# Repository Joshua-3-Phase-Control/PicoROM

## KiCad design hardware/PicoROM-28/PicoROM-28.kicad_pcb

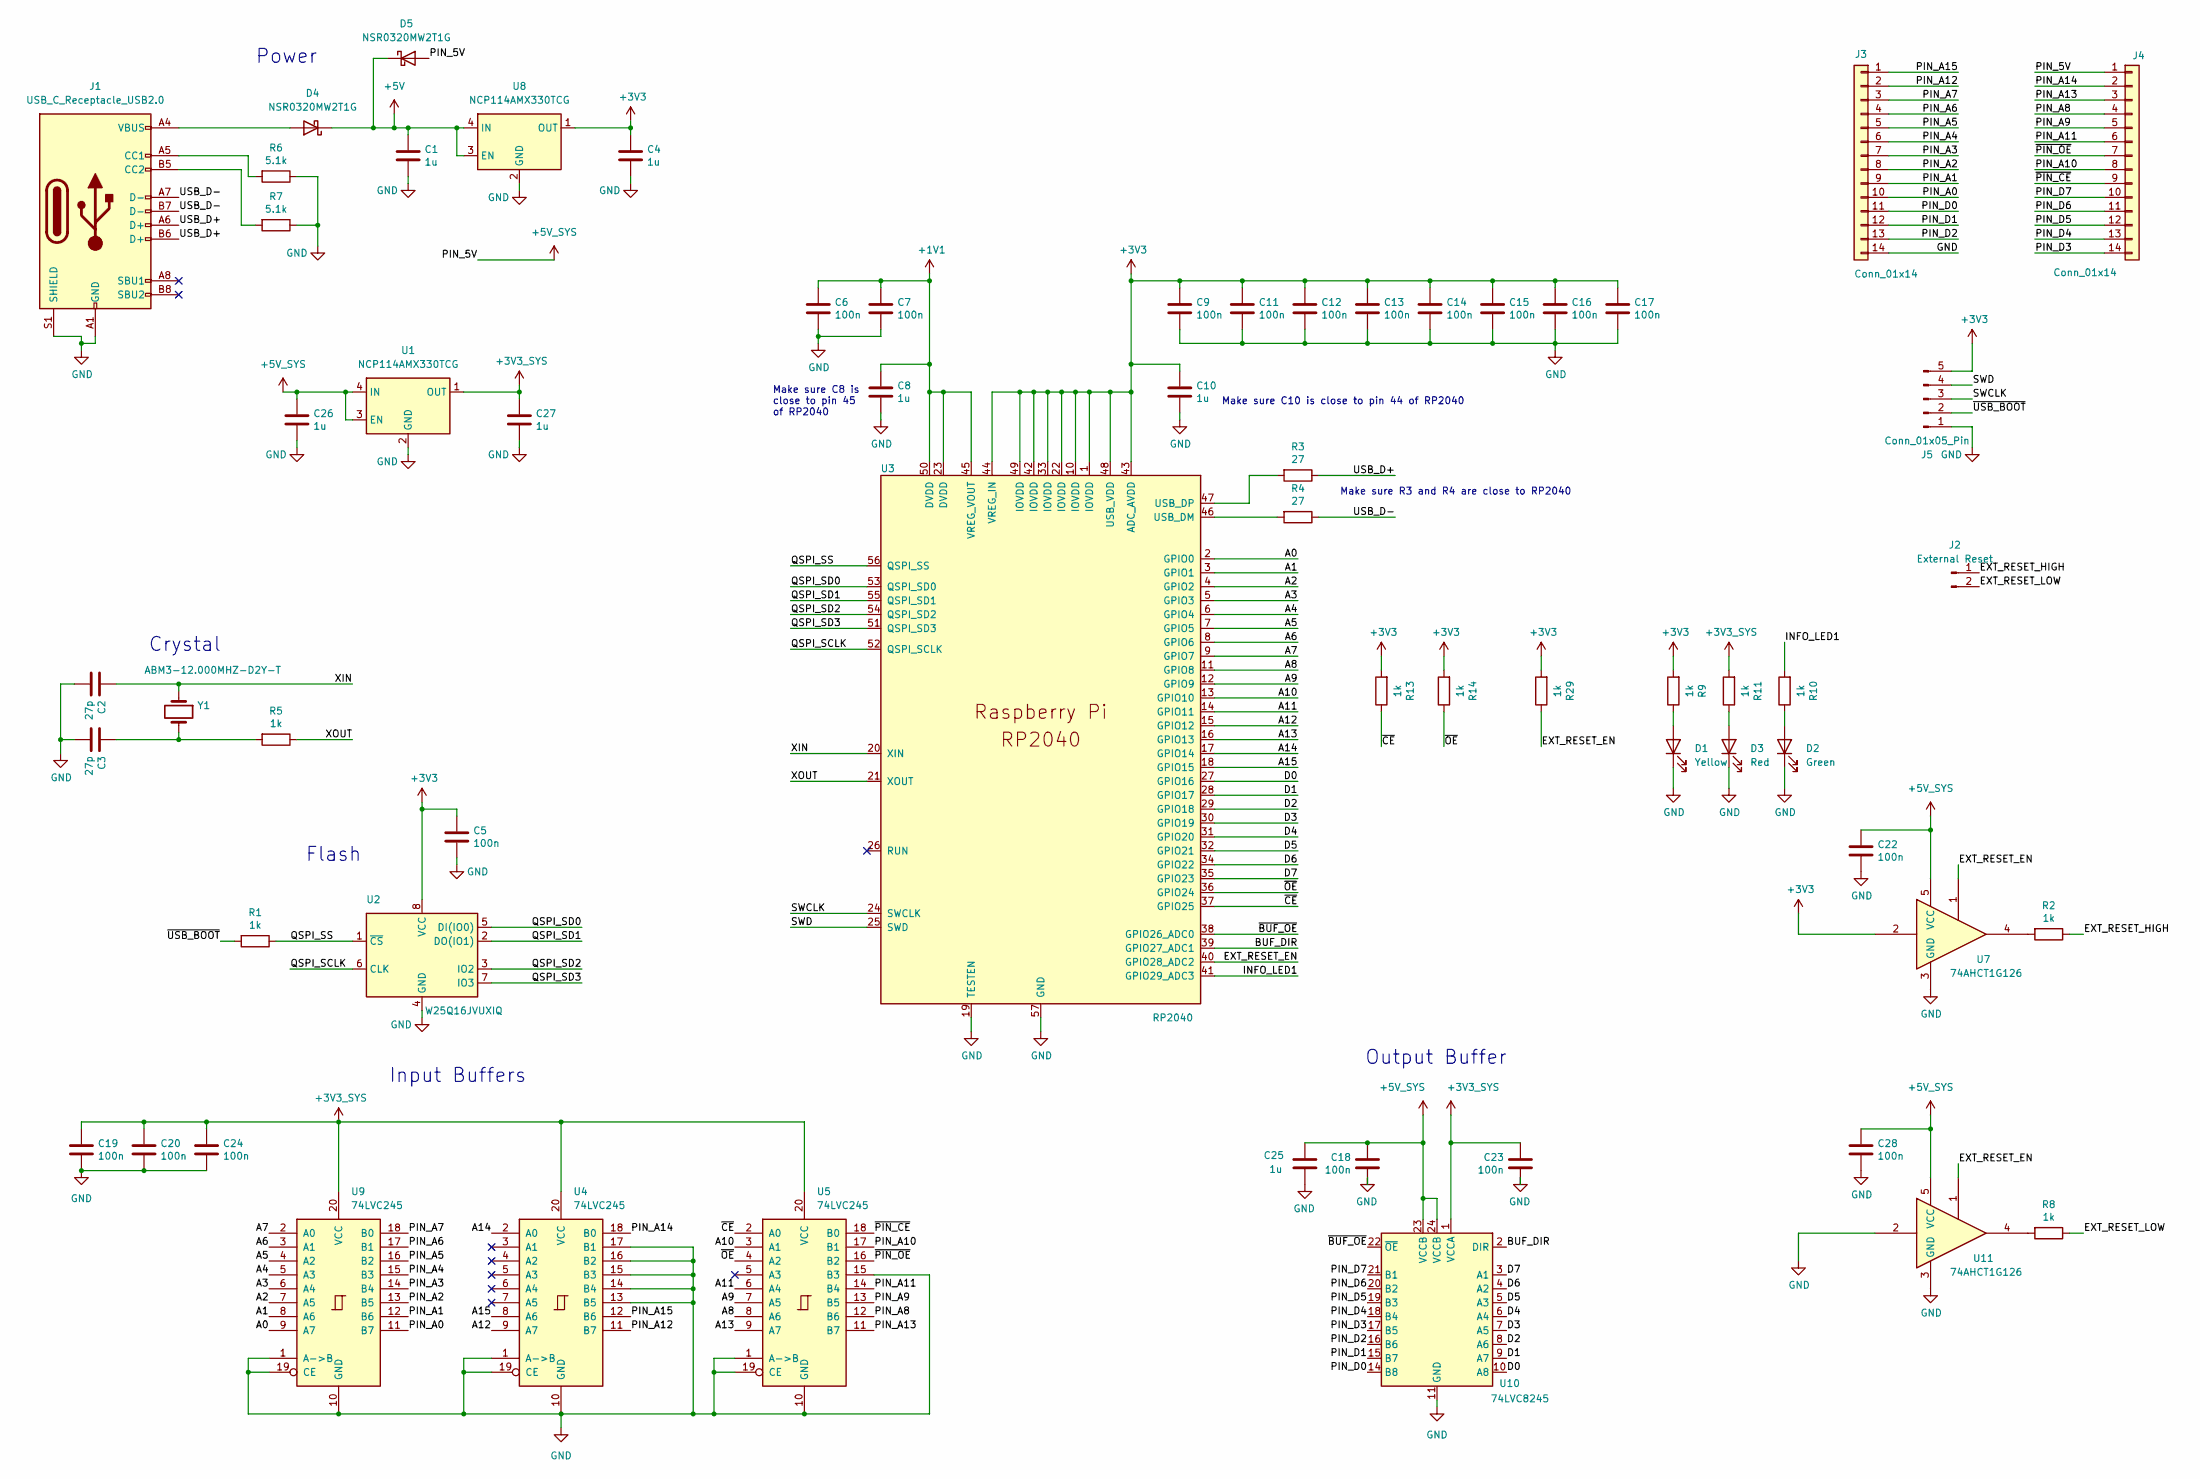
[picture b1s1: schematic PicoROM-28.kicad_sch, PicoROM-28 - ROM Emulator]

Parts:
C1, C4, C8, C10, C25, C26, C27: 1u; C_0402_1005Metric; MPN C52923
C2, C3: 27p; C_0402_1005Metric; MPN C1557
C5, C6, C7, C9, C11, C12, C13, C14, C15, C16, C17, C18, C19, C20, C22, C23, C24, C28: 100n; C_0201_0603Metric; MPN C307380
D1: Yellow; LED_0402_1005Metric; MPN C434450
D2: Green; LED_0402_1005Metric; MPN C74338
D3: Red; LED_0402_1005Metric; MPN C510305
D4, D5: NSR0320MW2T1G; D_SOD-323; MPN C48192
J1: USB_C_Receptacle_USB2.0; USB_C_Receptacle_HRO_TYPE-C-31-M-12; MPN C165948
J2: External Reset; PinHeader_1x02_P2.54mm_Vertical
J3, J4: Conn_01x14; PinHeader_1x14_P2.54mm_Vertical
J5: Conn_01x05_Pin; PinHeader_1x05_P1.27mm_Vertical
R1, R2, R5, R8, R9, R10, R11, R13, R14, R29: 1k; R_0201_0603Metric; MPN C270335
R3, R4: 27; R_0201_0603Metric; MPN C473051
R6, R7: 5.1k; R_0201_0603Metric; MPN C473460
U1, U8: NCP114AMX330TCG; OnSemi_XDFN4-1EP_1.0x1.0mm_EP0.52x0.52mm; MPN C133056
U2: W25Q16JVUXIQ; Winbond_USON-8-1EP_3x2mm_P0.5mm_EP0.2x1.6mm; MPN C7466821
U3: RP2040; RP2040-QFN-56; MPN C2040
U4, U5, U9: 74LVC245; V-QFN4525-20_L4.5-W2.5-P0.50-BL; MPN C294612
U7, U11: 74AHCT1G126; SOT-353_SC-70-5; MPN C52140433
U10: 74LVC8245; DHVQFN24_L5.5-W3.5-P0.50-BL-EP; MPN C548858
Y1: ABM3-12.000MHZ-D2Y-T; Crystal_SMD_5032-2Pin_5.0x3.2mm; MPN C148313

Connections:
+1V1: C6.1, C7.1, C8.1, U3.23 (DVDD), U3.45 (VREG_VOUT), U3.50 (DVDD)
+3V3: C4.1, C5.1, C9.1, C10.1, C11.1, C12.1, C13.1, C14.1, C15.1, C16.1, C17.1, J5.5, R9.2, R13.2, R14.2, R29.2, U2.8 (VCC), U3.1 (IOVDD), U3.10 (IOVDD), U3.22 (IOVDD), U3.33 (IOVDD), U3.42 (IOVDD), U3.43 (ADC_AVDD), U3.44 (VREG_IN), U3.48 (USB_VDD), U3.49 (IOVDD), U7.2, U8.1 (OUT)
+3V3_SYS: C19.1, C20.1, C23.1, C24.1, C27.1, R11.2, U1.1 (OUT), U4.20 (VCC), U5.20 (VCC), U9.20 (VCC), U10.1 (VCCA)
+5V: C1.1, D4.1 (K), D5.1 (K), U8.3 (EN), U8.4 (IN)
+5V_SYS: C18.1, C22.1, C25.1, C26.1, C28.1, D5.2 (A), J4.1, U1.3 (EN), U1.4 (IN), U7.5 (VCC), U10.23 (VCCB), U10.24 (VCCB), U11.5 (VCC)
/A0: U3.2 (GPIO0), U9.9 (A7)
/A1: U3.3 (GPIO1), U9.8 (A6)
/A2: U3.4 (GPIO2), U9.7 (A5)
/A3: U3.5 (GPIO3), U9.6 (A4)
/A4: U3.6 (GPIO4), U9.5 (A3)
/A5: U3.7 (GPIO5), U9.4 (A2)
/A6: U3.8 (GPIO6), U9.3 (A1)
/A7: U3.9 (GPIO7), U9.2 (A0)
/A8: U3.11 (GPIO8), U5.8 (A6)
/A9: U3.12 (GPIO9), U5.7 (A5)
/A10: U3.13 (GPIO10), U5.3 (A1)
/A11: U3.14 (GPIO11), U5.6 (A4)
/A12: U3.15 (GPIO12), U4.9 (A7)
/A13: U3.16 (GPIO13), U5.9 (A7)
/A14: U3.17 (GPIO14), U4.2 (A0)
/A15: U3.18 (GPIO15), U4.8 (A6)
/BUF_DIR: U3.39 (GPIO27_ADC1), U10.2 (DIR)
/D0: U3.27 (GPIO16), U10.10 (A8)
/D1: U3.28 (GPIO17), U10.9 (A7)
/D2: U3.29 (GPIO18), U10.8 (A6)
/D3: U3.30 (GPIO19), U10.7 (A5)
/D4: U3.31 (GPIO20), U10.6 (A4)
/D5: U3.32 (GPIO21), U10.5 (A3)
/D6: U3.34 (GPIO22), U10.4 (A2)
/D7: U3.35 (GPIO23), U10.3 (A1)
/EXT_RESET_EN: R29.1, U3.40 (GPIO28_ADC2), U7.1, U11.1
/EXT_RESET_HIGH: J2.1, R2.1
/EXT_RESET_LOW: J2.2, R8.1
/INFO_LED1: R10.2, U3.41 (GPIO29_ADC3)
/PIN_A0: J3.10, U9.11 (B7)
/PIN_A1: J3.9, U9.12 (B6)
/PIN_A2: J3.8, U9.13 (B5)
/PIN_A3: J3.7, U9.14 (B4)
/PIN_A4: J3.6, U9.15 (B3)
/PIN_A5: J3.5, U9.16 (B2)
/PIN_A6: J3.4, U9.17 (B1)
/PIN_A7: J3.3, U9.18 (B0)
/PIN_A8: J4.4, U5.12 (B6)
/PIN_A9: J4.5, U5.13 (B5)
/PIN_A10: J4.8, U5.17 (B1)
/PIN_A11: J4.6, U5.14 (B4)
/PIN_A12: J3.2, U4.11 (B7)
/PIN_A13: J4.3, U5.11 (B7)
/PIN_A14: J4.2, U4.18 (B0)
/PIN_A15: J3.1, U4.12 (B6)
/PIN_D0: J3.11, U10.14 (B8)
/PIN_D1: J3.12, U10.15 (B7)
/PIN_D2: J3.13, U10.16 (B6)
/PIN_D3: J4.14, U10.17 (B5)
/PIN_D4: J4.13, U10.18 (B4)
/PIN_D5: J4.12, U10.19 (B3)
/PIN_D6: J4.11, U10.20 (B2)
/PIN_D7: J4.10, U10.21 (B1)
/QSPI_SCLK: U2.6 (CLK), U3.52 (QSPI_SCLK)
/QSPI_SD0: U2.5 (DI(IO0)), U3.53 (QSPI_SD0)
/QSPI_SD1: U2.2 (DO(IO1)), U3.55 (QSPI_SD1)
/QSPI_SD2: U2.3 (IO2), U3.54 (QSPI_SD2)
/QSPI_SD3: U2.7 (IO3), U3.51 (QSPI_SD3)
/QSPI_SS: R1.1, U2.1 (~CS), U3.56 (QSPI_SS)
/SWCLK: J5.3, U3.24 (SWCLK)
/SWD: J5.4, U3.25 (SWD)
/USB_D+: J1.A6 (D+), J1.B6 (D+), R3.1
/USB_D-: J1.A7 (D-), J1.B7 (D-), R4.1
/XIN: C2.1, U3.20 (XIN), Y1.1
/XOUT: R5.1, U3.21 (XOUT)
/~BUF_OE: U3.38 (GPIO26_ADC0), U10.22 (~OE)
/~CE: R13.1, U3.37 (GPIO25), U5.2 (A0)
/~OE: R14.1, U3.36 (GPIO24), U5.4 (A2)
/~PIN_CE: J4.9, U5.18 (B0)
/~PIN_OE: J4.7, U5.16 (B2)
/~USB_BOOT: J5.2, R1.2
GND: C1.2, C2.2, C3.2, C4.2, C5.2, C6.2, C7.2, C8.2, C9.2, C10.2, C11.2, C12.2, C13.2, C14.2, C15.2, C16.2, C17.2, C18.2, C19.2, C20.2, C22.2, C23.2, C24.2, C25.2, C26.2, C27.2, C28.2, D1.1 (K), D2.1 (K), D3.1 (K), J1.A1 (GND), J1.A12 (GND), J1.B1 (GND), J1.B12 (GND), J1.S1 (SHIELD), J3.14, J5.1, R6.1, R7.1, U1.2 (GND), U1.5 (GND), U2.4 (GND), U3.19 (TESTEN), U3.57 (GND), U4.1 (A->B), U4.10 (GND), U4.13 (B5), U4.14 (B4), U4.15 (B3), U4.16 (B2), U4.17 (B1), U4.19 (CE), U5.1 (A->B), U5.10 (GND), U5.15 (B3), U5.19 (CE), U7.3 (GND), U8.2 (GND), U8.5 (GND), U9.1 (A->B), U9.10 (GND), U9.19 (CE), U10.11 (GND), U10.12 (GND), U10.13 (GND), U11.2, U11.3 (GND)
unnamed: C3.1, R5.2, Y1.2
unnamed: D1.2 (A), R9.1
unnamed: D2.2 (A), R10.1
unnamed: D3.2 (A), R11.1
unnamed: D4.2 (A), J1.A4 (VBUS), J1.A9 (VBUS), J1.B4 (VBUS), J1.B9 (VBUS)
unnamed: J1.A5 (CC1), R6.2
unnamed: J1.B5 (CC2), R7.2
unnamed: R2.2, U7.4
unnamed: R8.2, U11.4
unnamed: R4.2, U3.46 (USB_DM)
unnamed: R3.2, U3.47 (USB_DP)

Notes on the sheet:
Flash
Power
Make sure R3 and R4 are close to RP2040
Crystal
Input Buffers
Make sure C8 is close to pin 45 of RP2040
Output Buffer
Make sure C10 is close to pin 44 of RP2040

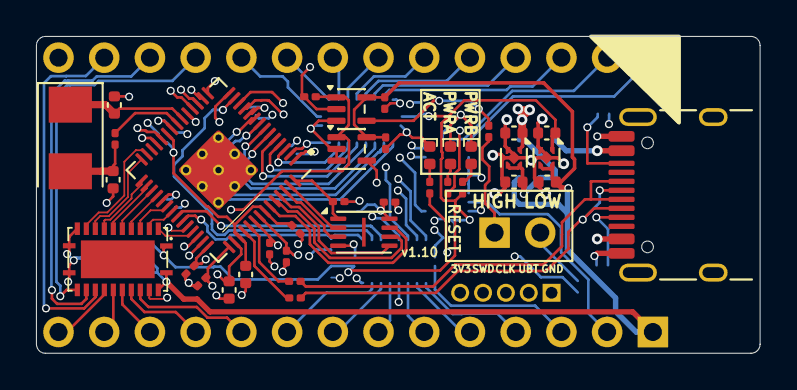
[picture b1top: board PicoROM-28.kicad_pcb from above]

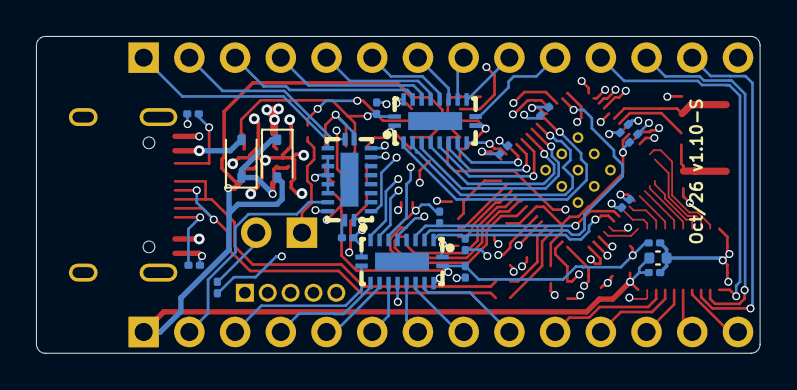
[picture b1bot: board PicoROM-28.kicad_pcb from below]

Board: 6 copper layers, 40.2 x 17.6 mm, 63 parts (24 on the bottom side), 88 nets.

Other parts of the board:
J6: 220-1-28-006; DIP-28_Adapter_CnCTech_220-1-28-006

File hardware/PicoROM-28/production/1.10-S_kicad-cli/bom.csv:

Designator,Footprint,Quantity,Value,LCSC Part #
"C1, C10, C25, C26, C27, C4, C8",0402,7,1u,C52923
"C11, C12, C13, C14, C15, C16, C17, C18, C19, C20, C22, C23, C24, C28, C5, C6, C7, C9",0201,18,100n,C307380
"C2, C3",0402,2,27p,C1557
D1,0402,1,Yellow,C434450
D2,0402,1,Green,C74338
D3,0402,1,Red,C510305
"D4, D5",D_SOD-323,2,NSR0320MW2T1G,C48192
J1,USB_C_Receptacle_HRO_TYPE-C-31-M-12,1,USB_C_Receptacle_USB2.0,C165948
"R1, R10, R11, R13, R14, R2, R29, R5, R8, R9",0201,10,1k,C270335
"R3, R4",0201,2,27,C473051
"R6, R7",0201,2,5.1k,C473460
"U1, U8",OnSemi_XDFN4-1EP_1.0x1.0mm_EP0.52x0.52mm,2,NCP114AMX330TCG,C133056
U10,DHVQFN24_L5.5-W3.5-P0.50-BL-EP,1,74LVC8245,C548858
"U11, U7",SOT-353_SC-70-5,2,74AHCT1G126,C52140433
U2,Winbond_USON-8-1EP_3x2mm_P0.5mm_EP0.2x1.6mm,1,W25Q16JVUXIQ,C7466821
U3,RP2040-QFN-56,1,RP2040,C2040
"U4, U5, U9",V-QFN4525-20_L4.5-W2.5-P0.50-BL,3,74LVC245,C294612
Y1,Crystal_SMD_5032-2Pin_5.0x3.2mm,1,ABM3-12.000MHZ-D2Y-T,C148313
